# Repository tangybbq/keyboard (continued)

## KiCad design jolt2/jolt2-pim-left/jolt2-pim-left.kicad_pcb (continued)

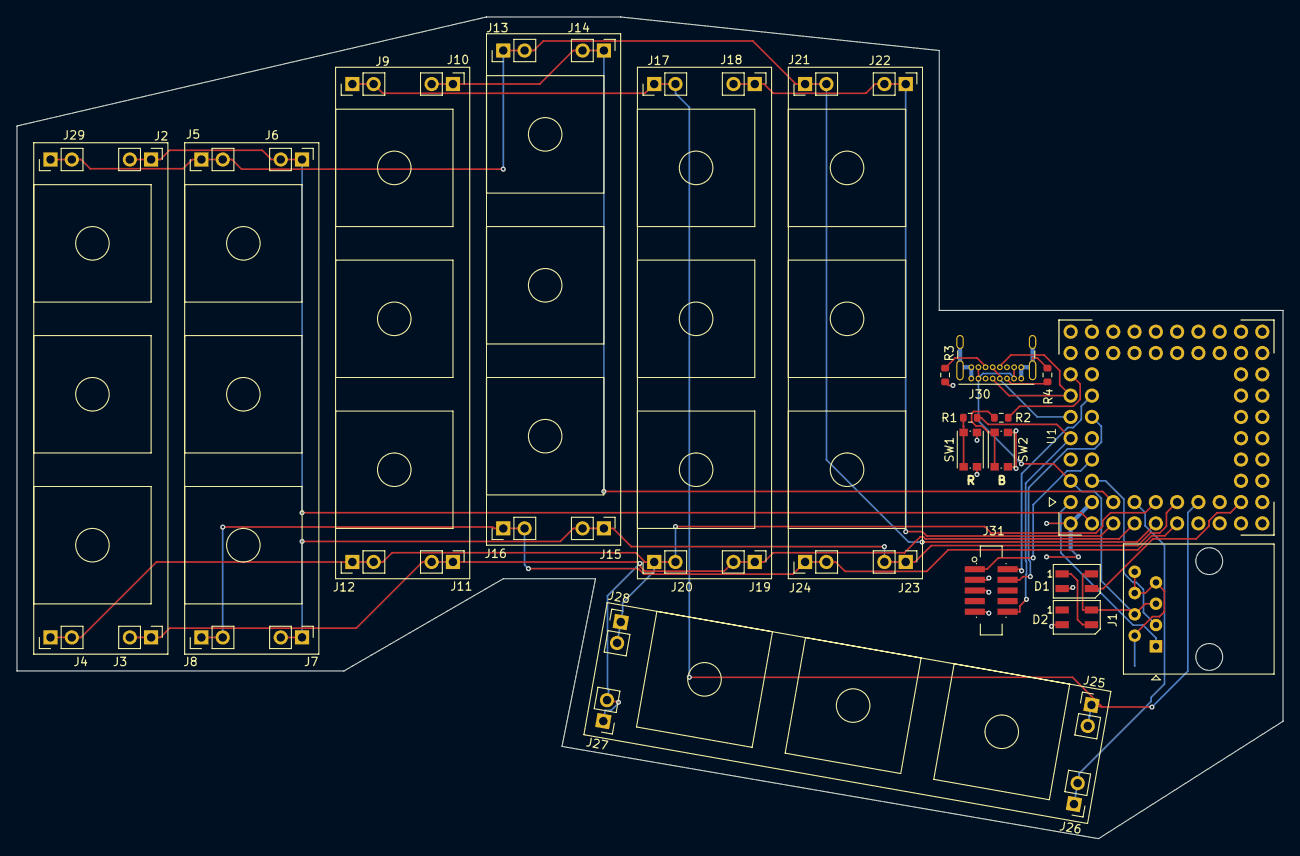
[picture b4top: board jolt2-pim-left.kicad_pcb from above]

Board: 2 copper layers, 151.0 x 98.0 mm, 40 parts (0 on the bottom side), 27 nets.
